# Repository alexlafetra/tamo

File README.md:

# Tamo

Tamo is an open source interdisciplinary hardware project designed to be both a piece of jewelry and a small being with (somewhat) complex emotions. This repository contains the firmware, hardware design (PCB & 3D files), graphics, and code for the web tools for sprite design and custom creature upload.

### Background

This project started as a way of making something that could be shared between people in my life that felt precious, but also mass-produced. It's designed to feel like it has an independent existence outside of just being your pet, like maybe it's "going through some shit," but also like you can effectively comfort it and have a connection to the creature inside Tamo.

### Modes

Tamo supports two modes: the default, "alive" mode and an "animation" mode: 

###### Animation
The animation mode is a very simple video player or slideshow which can loop over up to 16 frames of video at different speeds. It's designed more for tamo as a piece of jewelry, and doesn't feature any interaction other than turning tamo on/off with the main button.

###### Living
Living mode is the default mode for Tamo. While living, Tamo ages, speaks, gets hungry, gets happy, gets sad, gets angry, and eventually dies. Tamo can be afflicted by different maladies: a smoking habit, compulsive eating, mood swings, and depression. Tamo can be fed, talked to, or connected to another Tamo to swap places.

# Sprites
The [custom sprite designer](https://alexlafetra.github.io/tamo/designer.html?sprite) is a tool for creating animations & sprite art for tamo, which can be uploaded to the device using the browser and a USB-C cable.

The mode & creature identity can be set, and new sprites can be flashed to Tamo over USB, using [Tamo's website](https://alexlafetra.github.io/tamo/).

# Firmware

Tamo's firmware is a PlatformIO project built around Spence Konde's [megaTinyCore](https://github.com/SpenceKonde/megaTinyCore) and the Arduino framework, with a modified build process to allow for in-system flash reprogramming. This project uses [PlatformIO](https://platformio.org/) for compiling with a [custom linker script](/tamo/linker/sprites.ld) and to run a few python scripts that upload the EEPROM and custom fuses to the Attiny. Unfortunately, this project hasn't been ported to work as a standalone Arduino project, but this repository contains all the libraries and the platformio.ini file needed to setup the platformIO environment, hopefully making use of the platformIO extension for VSCode almost as beginner-friendly.

During compilation, a python script--`/scripts/compile_spritesheet.py`--automatically converts selected `.bmp` files inside the `/bitmaps` folder to C++ byte arrays and appends them to the main spritesheet array. The creature sprites selected by this script are randomly chosen each time from the 7 default creatures, so each tamo gets a different mix of sprite artwork to start with. Each of these creatures can be overwritten later, though.

A second script--`/scripts/build_eeprom.py`--builds a binary file with the default EEPROM values and writes it to the Attiny3217's EEPROM memory after the firmware upload.

## Uploading firmware

The Attiny3217 firmware is uploaded via its UPDI interface, which is exposed on the motherboard as three header pins (UPDI,GND, and VCC). For development, I've been using [pymcuprog](https://pypi.org/project/pymcuprog/) and this [Pico UART Bridge](https://github.com/Noltari/pico-uart-bridge) design to use a Pi Pico as a UPDI programmer and upload code to the Attiny. Any USB UPDI programmer should work, though!

###### Example of the Pico UART Bridge wired to the Tamo board's UPDI header pins as a programmer.

Although the UPDI headers are exposed on the board, the `SBU1/SBU2` pins on Tamo's USB-C jack are also both tied to the UPDI pin on the Attiny so the chip can be programmed using just a USB cable plugged into the USB-C port with the other end specially wired to a UPDI programmer. You'll need to make sure whatever cable you use for this carries the `SBU1/SBU2` lines, but this allows programming Tamo from inside its shell.

### A note about custom fuses & overwriteable flash

The Attiny has strict rules about which sections of flash memory can overwrite other sections -- code running in `BOOT` can overwrite `APPCODE` and `APPDATA` sections, but `BOOT` can never be overwritten (even by other code running from `BOOT`). By default, the *entire* memory of the Attiny is designated as the `BOOT` section, meaning the code uploaded to flash doesn't have permission to rewrite any part of the Attiny's memory.

So, to overwrite bitmap data during runtime (allowing the firmware to overwrite new artwork in the Attiny's flash without recompiling the firmware with new sprites) we need to ask the Attiny3217 to store the bitmap data in a section of its memory demarcated as `APPCODE` while still running the main code from the `BOOT` section. This just requires three things:

1. Creating a linker script which places the `spritesheet` variable containing all the bitmap data at a fixed memory address. This linker script is a copy of the default TinyMegaCore linker script, with a special section titled ".bitmap_data" added which has a specific, fixed address. 

2. The "spritesheet" variable in our C++ code needs a little linker flag to tell the linker to place it in that new ".bitmap_data" section:

```
const unsigned char spritesheet[]  __attribute__((section(".bitmap_data"))) = {
    ... DATA ...
};

```

2. Finally, the `BOOTEND` and `APPEND` fuses on the Attiny3217 need to be set during upload so that the `BOOT`/`APPCODE` partition is created, at the specific address of .bitmap_data, so that the .bitmap_data section is placed in `APPCODE`.

The addresses are written as `[APPEND page address, BOOTEND page address]` (the addresses values are actually the 256-byte *page* address, ie. 0x01 is byte 256, 0x02 is byte 512 etc.) For tamo, the `BOOTEND` fuse is set to `0x5E = 94`, meaning `94 x 256B = 24,064B` of flash is reserved for the main firmware running in `BOOT`, and the remaining ~8kB are used for bitmaps. The `APPEND` fuse is set to `0x00`, which tells the Attiny3217 to allocate the rest of flash from `BOOTEND` onwards for the `APPCODE` section.

To set these fuses using `pymcuprog`, run:

```
pymcuprog write --tool uart --device attiny3217 --uart {USB DEVICE PORT} --clk 230400 --memory fuses --offset 7 --literal 0x00 0x5E 
```
###### On Mac: The USB device will be something like ```/dev/cu.usbmodem14101```. Run ```ls /dev/tty.*``` in a terminal window to get a list of connected USB devices.

To read back the fuse values and check if they were written correctly, run:

```
pymcuprog read --tool uart --device attiny3217 --uart {USB DEVICE PORT} --clk 230400 --memory fuses
```

## Thank you's

This project is built with support from these other projects:

- [pymcuprog](https://pypi.org/project/pymcuprog/), for uploading and writing fuses via UPDI

- This [Pico UART Bridge](https://github.com/Noltari/pico-uart-bridge) project for building a custom UPDI programmer, so helpful!

- The code for the display was originally based on Datacute's [SSD1306 OLED Library](https://github.com/datacute/Tiny4kOLED), although now very heavily augmented

- The PCBs for this project were designed in [KiCad](https://www.kicad.org/) and specifically the battery charging schematic is based on the schematic for Adafruit's [MicroLipo Battery Charger](https://github.com/adafruit/Adafruit-MicroLipo-PCB)

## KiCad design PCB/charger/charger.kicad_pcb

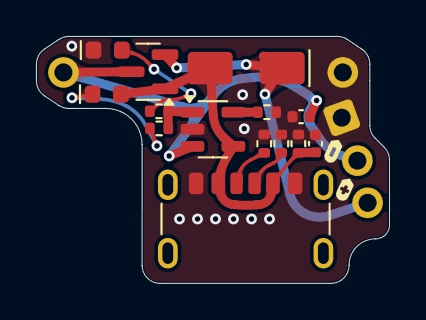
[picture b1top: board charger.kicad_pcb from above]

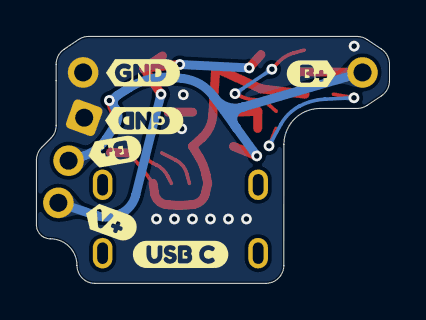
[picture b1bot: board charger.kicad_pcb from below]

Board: 2 copper layers, 19.6 x 13.7 mm, 26 parts (9 on the bottom side), 10 nets.

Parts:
C1, C2: 10µF; C_0402_1005Metric
D1, D2: LED; LED_0603_1608Metric
D3: SS14; D_SMA
J1: Conn_01x02_Socket; PinHeader_1x02_P2.54mm_Vertical
J2: USB_C_Receptacle; USB_C_Receptacle_GCT_USB4125-xx-x-0190_6P_TopMnt_Horizontal
J3, J4, J5: Conn_01x02_Socket; PinHeader_1x01_P2.54mm_Vertical
Q2: BSS83P; SOT-23
R1, R4: 5.1K; R_0402_1005Metric
R2, R3: 470; R_0402_1005Metric
R5: 20K; R_0402_1005Metric
R6: 4.7k; R_0402_1005Metric
U1: MCP73831T-2ACI/OT; SOT-23-5
kibuzzard-676F2A21: G***; kibuzzard-676F2A21
kibuzzard-676F29EF: G***; kibuzzard-676F29EF
kibuzzard-6770A34A: G***; kibuzzard-6770A34A
kibuzzard-6770A35D: G***; kibuzzard-6770A35D
kibuzzard-6770A330: G***; kibuzzard-6770A330
kibuzzard-6770A364: G***; kibuzzard-6770A364
kibuzzard-6770932C: G***; kibuzzard-6770932C
kibuzzard-6770936F: G***; kibuzzard-6770936F

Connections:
5V: C1.1, D1.2 (A), D3.2 (A), J2.A9 (VBUS), J2.B9 (VBUS), Q2.1 (G), R6.2, U1.4 (VDD)
CC1: J2.A5 (CC1), R4.2
CC2: J2.B5 (CC2), R1.2
GND: C1.2, C2.2, D2.1 (K), J1.2, J2.A12 (GND), J2.B12 (GND), J4.1, R1.1, R4.1, R5.2, R6.1, U1.2 (VSS)
unnamed: D1.1 (K), R2.1
unnamed: D2.2 (A), R3.1
unnamed: R5.1, U1.5 (PROG)
unnamed: R2.2, R3.2, U1.1 (STAT)
VBATT: C2.1, J1.1, J5.1, Q2.3 (D), U1.3 (VBAT)
VOUT: D3.1 (K), J3.1, Q2.2 (S)

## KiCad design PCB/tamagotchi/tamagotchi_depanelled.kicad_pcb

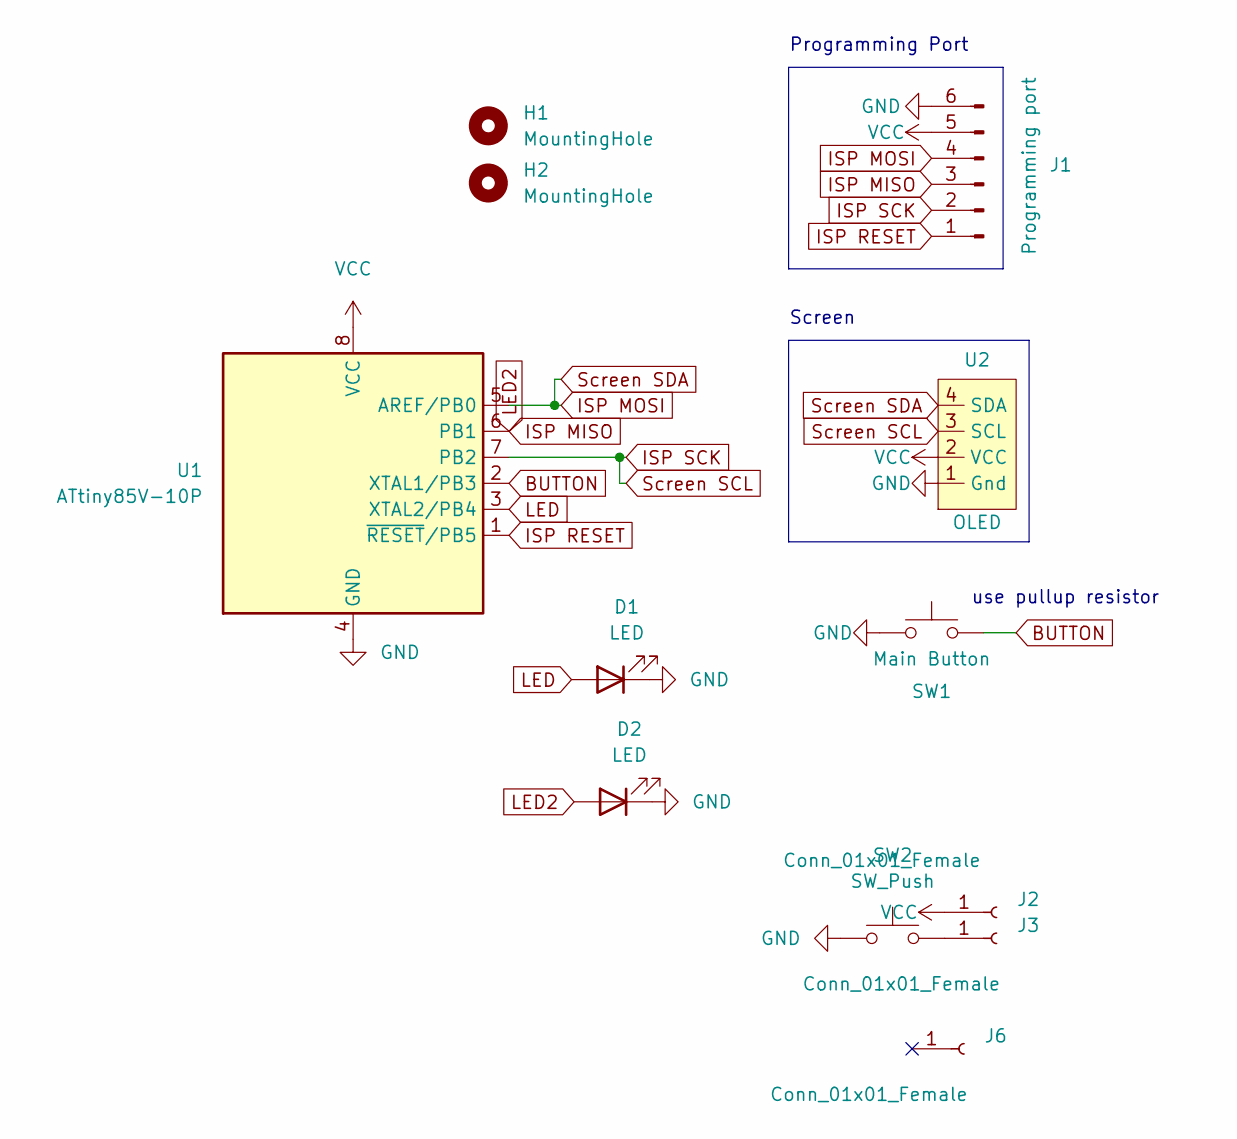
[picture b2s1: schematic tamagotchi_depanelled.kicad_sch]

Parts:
D1, D2: LED; LED_D1.8mm_W3.3mm_H2.4mm
H1, H2: MountingHole
J1: Programming port; PinHeader_1x06_P2.54mm_Vertical
J2, J3, J6: Conn_01x01_Female; PinHeader_1x01_P2.54mm_Vertical
SW1: Main Button; SW_PUSH_6mm
SW2: SW_Push; 18252321
U1: ATtiny85V-10P; DIP-8_W7.62mm
U2: OLED; Tiny OLED module

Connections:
BUTTON: SW1.2, U1.2 (XTAL1/PB3)
GND: D1.1 (K), D2.1 (K), J1.6, SW1.1, SW2.1, U1.4 (GND), U2.1 (Gnd)
ISP MISO: D2.2 (A), J1.3, U1.6 (PB1)
ISP MOSI: J1.4, U1.5 (AREF/PB0), U2.4 (SDA)
ISP RESET: J1.1, U1.1 (~RESET/PB5)
ISP SCK: J1.2, U1.7 (PB2), U2.3 (SCL)
LED: D1.2 (A), U1.3 (XTAL2/PB4)
unnamed: J3.1, SW2.2
VCC: J1.5, J2.1, U1.8 (VCC), U2.2 (VCC)

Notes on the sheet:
Programming Port
Screen
use pullup resistor

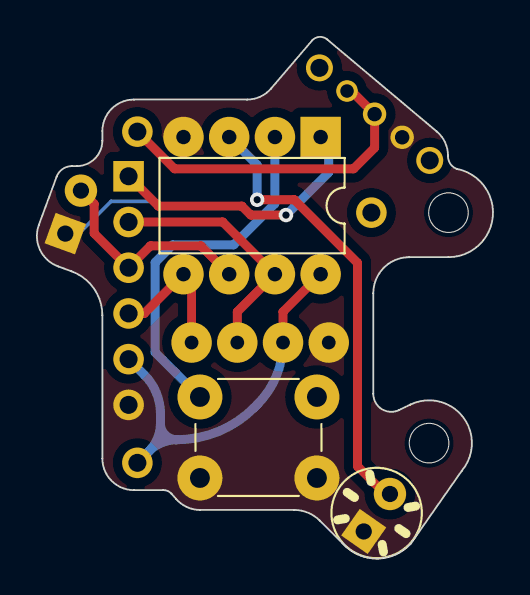
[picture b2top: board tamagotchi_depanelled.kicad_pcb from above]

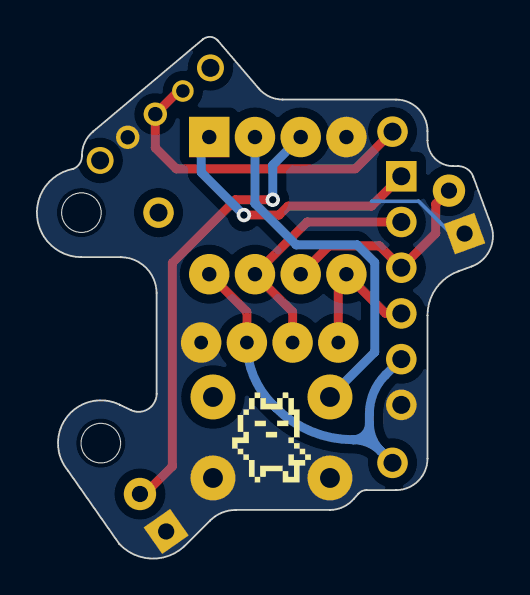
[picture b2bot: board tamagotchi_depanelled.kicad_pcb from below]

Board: 2 copper layers, 25.3 x 29.0 mm, 12 parts (4 on the bottom side), 9 nets.

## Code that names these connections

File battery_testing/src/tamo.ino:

/*

Tools > Board > attiny > 85
Port > (Arduino USB port)
Clock > Internal 8Mhz (i think this is accidentally swapped w 1mhz in arduino ide since it's slower)
Processor > Attiny85
Programmer > Arduino as ISP

*/

//https://github.com/Lorandil/ATTiny85-optimization-guide?tab=readme-ov-file

//If you need to debug the baby screen, use the 64x32 test sketch!
// #define TINY4KOLED_NO_PRINT
#define FULLSIZE//enable zoom in, 2x bitmaps

#include <TinyWireM.h>
//this library is modified!
// #include "Tiny4kOLEDprintless.h"
#include "Tiny4kOLED.h"

#include <avr/pgmspace.h>
#include <avr/sleep.h>
#include <avr/interrupt.h>
#include <avr/wdt.h>//to keep track of time
// #include <avr/power.h>    // Power management
// #include <EEPROM.h>

// #include <avr/io.h>
// #include <SoftwareSerial.h>

// SoftwareSerial Serial(3,4);

#define W 64
#define H 32

#define BUTTON_PIN 1
#define BATTERY_PIN 3

#define LED_PIN 4
#define RAND_PIN 5 //PB5 is the ISP reset pin, but also can be used to get a rand number? maybe?
#define AUX_LED_PIN 5 //second LED
#define BRIGHTNESS 16
//time (ms) before tamo sleeps
// #define TIME_BEFORE_SLEEP 120000
#define TIME_BEFORE_SLEEP 12000
#define LONG_PRESS_TIME 500;
#define DOUBLE_CLICK_TIME 100;
#define MAX_HUNGER 4320 // takes 12hr = 720min = 4320s to run out
#define MAX_MENTAL 8640 //takes 24hr to fully deplete

#define TAMO 0
#define BUG 1
#define CAT 2
#define PORCINI 3

#define CREATURE PORCINI

void ledOn(){
  analogWrite(LED_PIN,BRIGHTNESS);
}
void ledOff(){
  digitalWrite(LED_PIN,LOW);
}

using namespace std;

bool BUTTON = false;
bool LONG_PRESS = false;
bool DOUBLE_CLICK = false;

uint64_t lastTime = 0;
uint32_t timeOfLastButtonPress = 0;

bool itsbeen(uint32_t time){
  return((millis()-lastTime)>time);  
}

void readButtons();
void hardwareSleep();
void clearEdges();
void clearScreen();

#include "sprites.h"
#include "Animation.h"
#include "Tamo.h"
Tamo tamo;

/*
  Clears area to the right and left of main sprite
  so you don't need to do a full screen clear when switching
  between different sprites
*/

void clearEdges(){
  //left side
  oled.setCursor(0,0);
  oled.fillLength(0,16);
  oled.setCursor(0,1);
  oled.fillLength(0,16);

  //right side
  oled.setCursor(48,0);
  oled.fillLength(0,20);
  oled.setCursor(48,1);
  oled.fillLength(0,20);
}

//Clears visible area of screen
void clearScreen(){
  for (uint8_t m = 0; m < 2; m++) {
		oled.setCursor(0, m);
		oled.fillToEOP(0);
	}
}
//This is taken from:
//https://forum.arduino.cc/t/the-reliable-but-not-very-sexy-way-to-seed-random/65872
// void seedRandomNumberGenerator()

void readButtons(){
  bool val = !digitalRead(BUTTON_PIN);
  if(val){
    //if the button wasn't previously pressed, then it's a fresh press
    if(!BUTTON){
      if(millis()-timeOfLastButtonPress < 100){
        DOUBLE_CLICK = true;
      }
      else{
        DOUBLE_CLICK = false;
      }
      timeOfLastButtonPress = millis();
      LONG_PRESS = false;
    }
    analogWrite(LED_PIN,BRIGHTNESS);
    BUTTON = true;
    if((millis() - timeOfLastButtonPress) > (500) ){
      LONG_PRESS = true;
    }
  }
  else{
    digitalWrite(LED_PIN,LOW);
    //if the button *was* held, then you just released it
    if(BUTTON){
      if((millis() - timeOfLastButtonPress) > (500) ){
        LONG_PRESS = true;
      }
    }
    else{
      LONG_PRESS = false;
    }
    BUTTON = false;
  }
}

uint8_t pseudoRandom(uint8_t min, uint8_t max){
  return millis()%(max-min)+min;
}

void hardwareSleepCheck(){
  if(itsbeen(TIME_BEFORE_SLEEP)){
    hardwareSleep();
  }
}

void hardwareSleep(){
  //turn off OLED, LED
  oled.off();
  digitalWrite(LED_PIN,LOW);

  // //https://bigdanzblog.wordpress.com/2014/08/10/attiny85-wake-from-sleep-on-pin-state-change-code-example/
  GIMSK |= _BV(PCIE);                     // Enable Pin Change Interrupts
  // PCMSK |= _BV(PCINT3);                   // Use PB3 as interrupt pin
  PCMSK |= _BV(PCINT1);                   // Use PB1 as interrupt pin

  set_sleep_mode(SLEEP_MODE_PWR_DOWN);   // sleep mode is set here
  sleep_enable();                          // enables the sleep bit in the mcucr register so sleep is possible  
  sleep_cpu();                            // sleep (idk what the diff is)
}

//Interrupt callback to wake Attiny back up
ISR(PCINT0_vect){
  sleep_disable();                       // first thing after waking from sleep: disable sleep...
  clearScreen();
  // PCMSK &= ~_BV(PCINT3);                  // Turn off PB3 as interrupt pin
  PCMSK &= ~_BV(PCINT1);                  // Turn off PB3 as interrupt pin
  oled.on();//turn screen back on
}


// Timer0 overflow interrupt, this triggers every 10 seconds!
// ISR(WDT_vect) {
//   tamo.body();//tamo gets hungrier
// }

void initOled(){
  //start i2c communication w little oled
  oled.begin(72, 40, sizeof(tiny4koled_init_72x40br), tiny4koled_init_72x40br);
  #ifdef FULLSIZE
  // oled.enableZoomIn();//Need this so the sprites aren't all weird
  #endif
  oled.setRotation(2);//flip display upside-down
  oled.on();
  oled.clear();
}

//lights up screen and LED until batt dies
void batteryStressTest(){
  oled.fill(0xFF);
  // analogWrite(LED_PIN,BRIGHTNESS);
  digitalWrite(LED_PIN,HIGH);
}

void testADC(){
  oled.clear();  
  uint16_t quantVal = analogRead(BUTTON_PIN);
  //each val here is 8px tall, bc of how OLED pages work
  const uint8_t length = 16;
  uint8_t displayVal [length];
  for(uint8_t i = 0; i<length; i++){
    displayVal[i] = 0;
  }
  // uint8_t numberOf1s = quantVal * float(length)/float(255);
  // for(uint8_t i = 0; i<numberOf1s; i++){
  //   displayVal[i] = 255;
  // }
  // oled.renderFBO2x(16,0,length,0,displayVal);
}

// #define INTERNAL2V56_NO_CAP (6)

void setup() {
  //turn ADC off
  // ADCSRA &= ~_BV(ADEN);

  /*
      Initializing I/O 
  */
  //main button
  DDRB &= ~(1 << PB1); // Set the button pin PB3 as input (main button)
  PORTB |= (1 << PB1);  //activate pull-up resistor for PB3 (main button connects PB3 to GND)
  //ADC3
  // analogReference( INTERNAL2V56_NO_CAP );
  // analogReference( INTERNAL1V1 );
  // pinMode(BATTERY_PIN,INPUT);

  

  /*
      Turning on LED control
  */
  DDRB |= ( 1 << PB4 );  //set led pin to output
  digitalWrite(LED_PIN,LOW);

  /*
      Turning on watchdog timer
  */
  // WDTCR = (1 << WDCE) | (1 << WDE); // Enable changes to WDT
  // WDTCR = (1 << WDP3) | (1 << WDP0) | (1 << WDIE); // Set prescaler to 1s and enable interrupt

  // Enable global interrupts
  sei();
  
  initOled();
  oled.setFont(FONT6X8);
}

//had to ask the LLM for this one
/*
Basically, according to gpt, analogread always compares the pin value to VCC (meaning you can't read VCC -- it'll always be 1024)
but you CAN measure the internal voltages using the ADC, which basically let's you measure VCC backwards.
*/
uint16_t chatGPTReadVoltage(){
  ADCSRA |= 1<<ADEN;                          // Enable the ADC
  // Read 1.1V reference against AVcc
  ADMUX = _BV(MUX3) | _BV(MUX2); // Select internal 1.1V (on ATTiny85)
  delay(2); // Wait for Vref to settle
  ADCSRA |= _BV(ADSC); // Start conversion
  while (bit_is_set(ADCSRA, ADSC)); // Wait until done
  uint16_t result = ADC;

  //turn ADC off
  ADCSRA &= ~_BV(ADEN);
  return result;
}


uint16_t batteryValue = 0;

void readBattVoltage(){
  uint16_t value = chatGPTReadVoltage();
  if(value != batteryValue){
    batteryValue = value;
    String s = String(batteryValue);
    while(s.length() < 5){
      s = "0"+s;
    }
    oled.setCursor(6,0);
    oled.print(s);
  }
}

void loop() {
  // batteryStressTest();
  readBattVoltage();
  // digitalWrite(LED_PIN,(millis()/200)%2);
  // tamo.feel();
}

/*
Calibration notes:
@5V it's ~212
@3.9V it's ~260
@3.73 it's ~295
@3.3V it's ~358
@1.57 it's ~703

voltage = -150.70169*(measurement)+893.05592

*/

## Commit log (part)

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2024-07-26 first commit!
2024-07-26 Uhh... okay
    mood cycle is now less buggy and easier to change, interrupt from sleep works correctly, oled screen clearing is quicker, sprite updates, new thoughts, no glitchy sprites (so far!)
2024-07-31 added 3d files, pcb files
2024-07-31 gitignore stuff
2024-10-25 optimized animation system
2024-10-25 optimized
2024-10-25 src got deleted! replacing it
2024-10-25 not sure!
2024-10-25 merging in optimizations
2024-10-25 file organizing
2024-10-25 setting up for tiny wireframes
2024-10-25 created fbo class
2024-10-29 tweaks
2024-10-31 trying to get framebuffers working
2024-11-02 a lot!
    okay so gave up on wireframe stuff and instead implemented ageing/hunger. Also added alternate sprites, and started refining the interactivity model
2025-01-01 reorganizing repo
2025-01-01 added case models
2025-01-11 adding gifs
2025-02-16 finalizing attiny85 version
2025-03-31 palestine flag & arabic
2025-04-01 crunched all the oled code into one file
2025-05-05 Not sure what i changed!
    New case, new working battery reading code
2025-05-05 Added switchable sprites
2025-05-09 added a lot!
    - bitmap combining for a smaller file size
    - some rough eeprom prototyping
    - the ability to use two tamo spritesheets (for diff creatures, randomly chosen)
    - redid some sprites
    - cleaned up/tried to optimize as much code as possible
2025-05-09 Optimization
    Refactored some code and added in BUG
2025-09-22 adding in bitmap compilation script
2025-09-22 added in bitmap compiling
2025-10-01 added font for debugging
2025-10-15 reorganizing build scripts
2025-10-19 Adding to readme, updating sprites
2025-10-19 Spritesheet update
    - All bitmaps live on one big spritesheet now
2025-10-19 Added new food! & Food preference
2025-10-20 Refactored enums into #defines
2025-11-17 added in custom ISP programmer files
2026-01-23 idek man
2026-01-26 added penny/food preference logic
2026-02-09 penny
2026-03-28 rebirth bugfix
2026-04-10 bugfixing/implementing double click
2026-04-14 big attiny3217 update
    - ported pins, interrupts (not ADC yet)
    - added in FBO support, some new transition animations
    - also! tinyOLED is much smaller than Adafruit GFX+SSD1306, so the project is keeping it and trimming it even more to just what's necessary for tamo
2026-04-18 testing UART, removing PROGMEM
2026-04-22 initial sprite designer commit
2026-04-22 porting tamo_designer
2026-04-22 reorganizing repo structure
2026-04-23 some bugfixing of the spritedesigner, better css layout on mobile
2026-04-23 layout edits, fixing export bugs
2026-04-24 updating some graphics, cleaning up libraries
2026-04-24 fixing upload bugs, tweaking layout of webpage
2026-04-25 pivoting to flash rewrite!
2026-04-26 sprite upload working! flash write
2026-04-27 "set identity" functionality
    - started redoing README
    - added new default sprite, Excalibur
    - added custom gifs for each "identity"
2026-05-16 updating for v1.0 boards
2026-05-18 testing landing page
2026-05-19 testing landing page again
2026-05-31 big update to the website
2026-06-01 designer visual overhaul/semifinal polishing
    not working: dragging frames
2026-06-01 designer UI polishing
2026-06-06 implementing slideshow/editor
2026-06-07 organizing homepage, graphical tweaks to darkmode
2026-06-07 polishing main menu
2026-06-09 little polishing
